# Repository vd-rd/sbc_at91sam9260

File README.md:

## Description
The second installment in the embedded Linux hardware development learning exercise.
The board is an updated version of the previous [AT91RM9200_SBC](https://github.com/vd-rd/sbc_at91rm9200/).
Detailed documentation and resources can be found in the [docs](docs) and [resources](resources) folders.

Note: the CPU comes in two variants, 208 pin PQFP and 217 pin BGA. The PFQP version is pin compatible with AT91SAM9XE. The BGA version is compatible with the improved AT91SAM9G20 and has its own [board](https://github.com/vd-rd/sbc_at91sam9g20).

### Features
 * CPU - AT91SAM9260 processor (ARM926EJ @ 200MHz)
 * RAM - 1Gb SDRAM max ( 3V3 and 1V8 types supported)
 * NVM - AT45DB dataflash for U-boot
 * microSD card slot
 * microUSB client interface
 * USB host breakout
 * RMII interface for Ethernet
 * standard Apollo.IoT expansion header

### Resources
You can find all necesary information to build or evaluate the module here:
   - [View layout and schematic](https://cadlab.io/project/1695) 
   - [View 3D board render](https://a360.co/2PfLcwq)
   - [Fabrication files](https://github.com/vd-rd/sbc_at91sam9260/releases)

### Current status and changelog
  - v1.1.0 assembled and tested using SAM-BA, AT91Bootstrap, U-Boot and Linux Kernel ported from AT91SAM9260EK and running ok
  - v1.1.0 sent to factory, expected to be ready for assembly and testing in mid June.
  - 17feb2021 - v1.1.0 assembled. Debug via UART and USB functional.
  - 19feb2021 - sam-ba is able to load applets. AT91Bootstrap configured and flashed starting from at91sam9260ekdf_uboot_defconfig
  - 21feb2021 - Preliminary uBoot configured and flashed starting from at91sam9260ek_defconfig

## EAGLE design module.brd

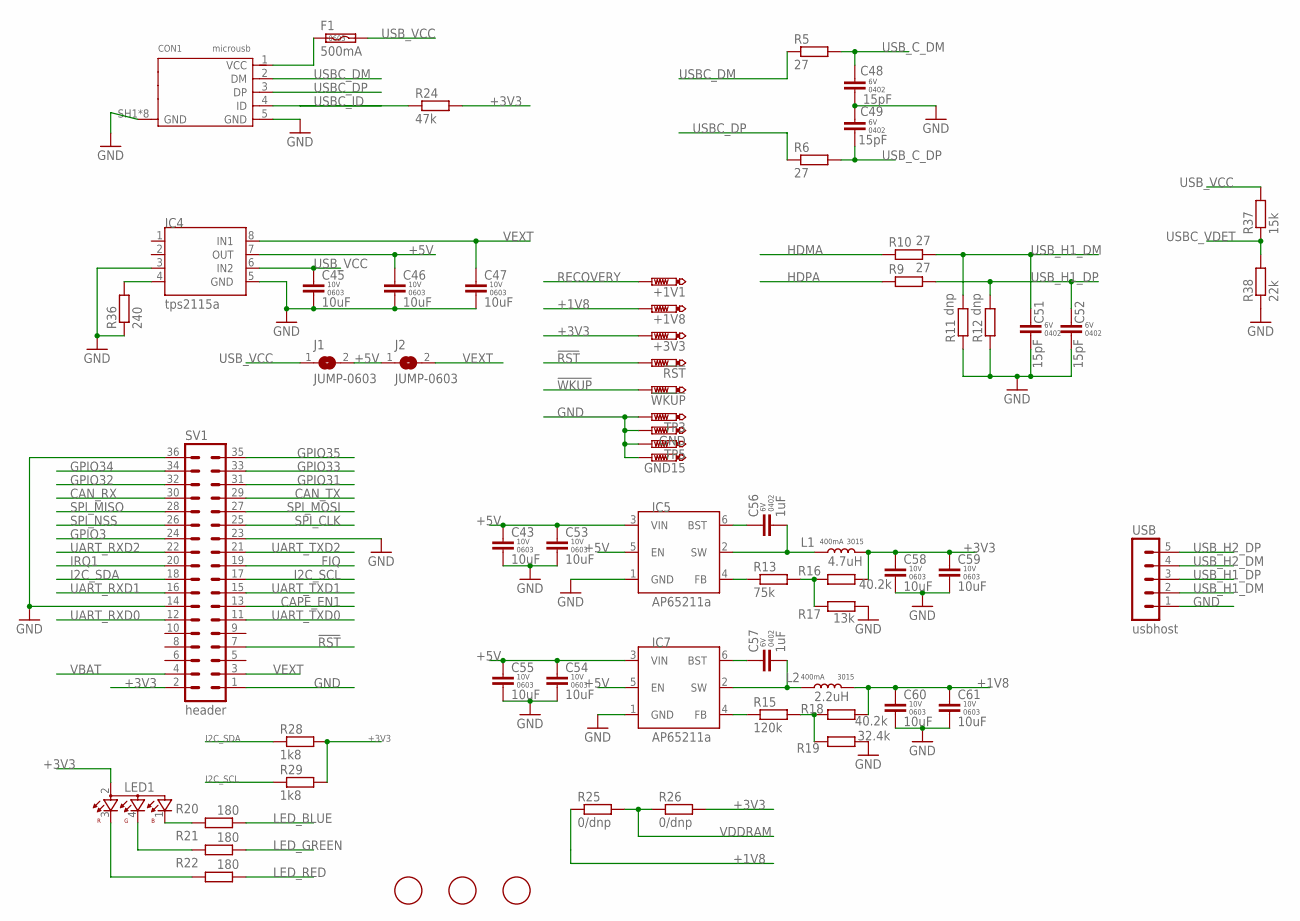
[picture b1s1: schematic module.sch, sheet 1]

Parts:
!RST: PTR1B1,27; B1,27
!WKUP: PTR1B1,27; B1,27
+1V1, +1V8, +3V3: PTR1B1,27; B1,27
C43, C45, C46, C47, C53, C54, C55, C58, C59, C60, C61: 10uF; C0603
C48, C49, C51, C52: 15pF; C0402K
C56, C57: 1uF; C0402K
CON1: microusb; 10118194
F1: 500mA; F0603
GND, GND15: PTR1B1,27; B1,27
IC4: tps2115a; TSSOP8
IC5, IC7: AP65211; SOT95P280X110-6
J1, J2: JUMP-0603; C0603
L1: 4.7uH; L3230M
L2: 2.2uH; L3230M
LED1: OSTB1204C1E; 321015RGB
R5, R6, R9, R10: 27; R0402
R11, R12: dnp; R0402
R13: 75k; R0402
R15: 120k; R0402
R16, R18: 40.2k; R0402
R17: 13k; R0402
R19: 32.4k; R0402
R20, R21, R22: 180; R0402
R24: 47k; R0402
R25, R26: 0/dnp; R0603
R28, R29: 1k8; R0402
R36: 240; R0402
R37: 15k; R0402
R38: 22k; R0402
SV1: header; MA18-2
TP3, TP5: PTR1B1,27; B1,27
U$1, U$2, U$3: FIDUCIAL; FIDUCIAL_1MM
USB: usbhost; MA05-1

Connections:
!RST: !RST.TP, SV1.7; also elsewhere on the board
!WKUP: !WKUP.TP; also elsewhere on the board
+1V8: +1V8.TP, C60.1, C61.1, L2.2, R18.2, R25.1; also elsewhere on the board
+3V3: +3V3.TP, C58.1, C59.1, L1.2, LED1.2, R16.2, R24.2, R26.2, R28.2, R29.2, SV1.2; also elsewhere on the board
+5V: C43.1, C46.1, C53.1, C54.1, C55.1, IC4.7 (OUT), IC5.3 (VIN), IC5.5 (EN), IC7.3 (VIN), IC7.5 (EN), J1.2, J2.1
CAN_RX: SV1.30
CAN_TX: SV1.29
CAPE_EN1: SV1.13; also elsewhere on the board
FIQ: SV1.19; also elsewhere on the board
GND: C43.2, C45.2, C46.2, C47.2, C48.2, C49.2, C51.2, C52.2, C53.2, C54.2, C55.2, C58.2, C59.2, C60.2, C61.2, CON1.5 (GND), CON1.SH1 (GND), CON1.SH2 (GND), CON1.SH3 (GND), CON1.SH4 (GND), CON1.SH5 (GND), CON1.SH6 (GND), CON1.SH7 (GND), CON1.SH8 (GND), GND.TP, GND15.TP, IC4.3, IC4.5 (GND), IC5.1 (GND), IC7.1 (GND), R11.1, R12.1, R17.2, R19.2, R36.1, R38.1, SV1.1, SV1.14, SV1.23, SV1.36, TP3.TP, TP5.TP, USB.1; also elsewhere on the board
GPIO3: SV1.24; also elsewhere on the board
GPIO31: SV1.31; also elsewhere on the board
GPIO32: SV1.32; also elsewhere on the board
GPIO33: SV1.33; also elsewhere on the board
GPIO34: SV1.34; also elsewhere on the board
GPIO35: SV1.35; also elsewhere on the board
HDMA: R10.1; also elsewhere on the board
HDPA: R9.1; also elsewhere on the board
I2C_SCL: R29.1, SV1.17; also elsewhere on the board
I2C_SDA: R28.1, SV1.18; also elsewhere on the board
IRQ1: SV1.20; also elsewhere on the board
LED_BLUE: R20.1; also elsewhere on the board
LED_GREEN: R21.1; also elsewhere on the board
LED_RED: R22.1; also elsewhere on the board
unnamed: C56.2, IC5.2 (SW), L1.1
unnamed: CON1.1 (VCC), F1.1
unnamed: IC4.4, R36.2
unnamed: C57.2, IC7.2 (SW), L2.1
unnamed: LED1.1, R20.2
unnamed: C56.1, IC5.6 (BST)
unnamed: C57.1, IC7.6 (BST)
unnamed: LED1.4, R21.2
unnamed: IC7.4 (FB), R15.1
unnamed: IC5.4 (FB), R13.1
unnamed: R15.2, R18.1, R19.1
unnamed: R13.2, R16.1, R17.1
unnamed: LED1.3, R22.2
RECOVERY: +1V1.TP; also elsewhere on the board
SPI_CLK: SV1.25; also elsewhere on the board
SPI_MISO: SV1.28; also elsewhere on the board
SPI_MOSI: SV1.27; also elsewhere on the board
SPI_NSS: SV1.26; also elsewhere on the board
UART_RXD0: SV1.12; also elsewhere on the board
UART_RXD1: SV1.16; also elsewhere on the board
UART_RXD2: SV1.22; also elsewhere on the board
UART_TXD0: SV1.11; also elsewhere on the board
UART_TXD1: SV1.15; also elsewhere on the board
UART_TXD2: SV1.21; also elsewhere on the board
USBC_DM: CON1.2 (DM), R5.1
USBC_DP: CON1.3 (DP), R6.1
USBC_ID: CON1.4 (ID), R24.1; also elsewhere on the board
USBC_VDET: R37.1, R38.2; also elsewhere on the board
USB_C_DM: C48.1, R5.2; also elsewhere on the board
USB_C_DP: C49.1, R6.2; also elsewhere on the board
USB_H1_DM: C51.1, R10.2, R11.2, USB.2
USB_H1_DP: C52.1, R9.2, R12.2, USB.3
USB_H2_DM: USB.4
USB_H2_DP: USB.5
USB_VCC: C45.1, F1.2, IC4.6 (IN2), J1.1, R37.2
VBAT: SV1.4
VDDRAM: R25.2, R26.1; also elsewhere on the board
VEXT: C47.1, IC4.8 (IN1), J2.2, SV1.3

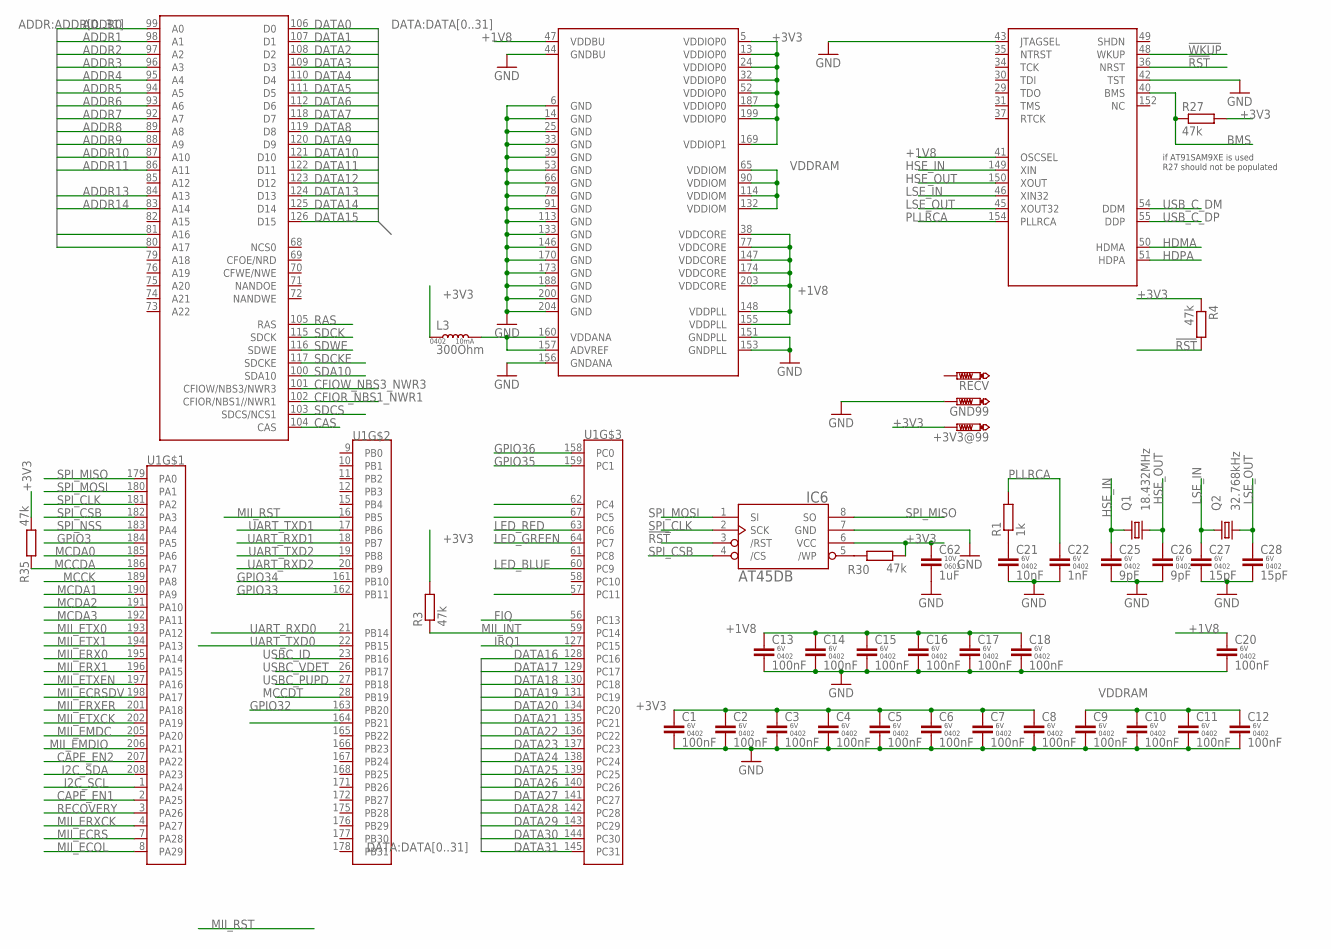
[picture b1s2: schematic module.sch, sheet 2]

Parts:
+3V3@99: PTR1B1,27; B1,27
C1, C2, C3, C4, C5, C6, C7, C8, C9, C10, C11, C12, C13, C14, C15, C16, C17, C18, C20: 100nF; C0402K
C21: 10nF; C0402K
C22: 1nF; C0402K
C25, C26: 9pF; C0402K
C27, C28: 15pF; C0402K
C62: 1uF; C0603
GND99: PTR1B1,27; B1,27
IC6: AT45DB-S; SO08-208
L3: 300Ohm; L0402
Q1: 18.432MHz; 3215
Q2: 32.768kHz; 3215
R1: 1k; R0402
R3, R4, R27, R30, R35: 47k; R0402
RECV: PTR1B1,27; B1,27
U1: AT91SAM9260-; QFP50P3120X3120X410-208N

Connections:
!RST: IC6.3 (/RST), R4.2, U1.36 (NRST); also elsewhere on the board
!WKUP: U1.48 (WKUP); also elsewhere on the board
+1V8: C13.1, C14.1, C15.1, C16.1, C17.1, C18.1, C20.1, U1.38 (VDDCORE), U1.41 (OSCSEL), U1.47 (VDDBU), U1.77 (VDDCORE), U1.147 (VDDCORE), U1.148 (VDDPLL), U1.155 (VDDPLL), U1.174 (VDDCORE), U1.203 (VDDCORE); also elsewhere on the board
+3V3: +3V3@99.TP, C1.1, C2.1, C3.1, C4.1, C5.1, C6.1, C7.1, C8.1, C62.1, IC6.6 (VCC), L3.1, R3.2, R4.1, R27.2, R30.2, R35.2, U1.5 (VDDIOP0), U1.13 (VDDIOP0), U1.24 (VDDIOP0), U1.32 (VDDIOP0), U1.52 (VDDIOP0), U1.169 (VDDIOP1), U1.187 (VDDIOP0), U1.199 (VDDIOP0); also elsewhere on the board
ADDR0: U1.99 (A0); also elsewhere on the board
ADDR1: U1.98 (A1); also elsewhere on the board
ADDR2: U1.97 (A2); also elsewhere on the board
ADDR3: U1.96 (A3); also elsewhere on the board
ADDR4: U1.95 (A4); also elsewhere on the board
ADDR5: U1.94 (A5); also elsewhere on the board
ADDR6: U1.93 (A6); also elsewhere on the board
ADDR7: U1.92 (A7); also elsewhere on the board
ADDR8: U1.89 (A8); also elsewhere on the board
ADDR9: U1.88 (A9); also elsewhere on the board
ADDR10: U1.87 (A10); also elsewhere on the board
ADDR11: U1.86 (A11); also elsewhere on the board
ADDR13: U1.84 (A13); also elsewhere on the board
ADDR14: U1.83 (A14); also elsewhere on the board
ADDR16: U1.81 (A16); also elsewhere on the board
ADDR17: U1.80 (A17); also elsewhere on the board
BMS: R27.1, U1.40 (BMS)
CAPE_EN1: U1.2 (PA25); also elsewhere on the board
CAPE_EN2: U1.207 (PA22)
CAS: U1.104 (CAS); also elsewhere on the board
CFIOR_NBS1_NWR1: U1.102 (CFIOR/NBS1//NWR1); also elsewhere on the board
CFIOW_NBS3_NWR3: U1.101 (CFIOW/NBS3/NWR3); also elsewhere on the board
DATA0: U1.106 (D0); also elsewhere on the board
DATA1: U1.107 (D1); also elsewhere on the board
DATA2: U1.108 (D2); also elsewhere on the board
DATA3: U1.109 (D3); also elsewhere on the board
DATA4: U1.110 (D4); also elsewhere on the board
DATA5: U1.111 (D5); also elsewhere on the board
DATA6: U1.112 (D6); also elsewhere on the board
DATA7: U1.118 (D7); also elsewhere on the board
DATA8: U1.119 (D8); also elsewhere on the board
DATA9: U1.120 (D9); also elsewhere on the board
DATA10: U1.121 (D10); also elsewhere on the board
DATA11: U1.122 (D11); also elsewhere on the board
DATA12: U1.123 (D12); also elsewhere on the board
DATA13: U1.124 (D13); also elsewhere on the board
DATA14: U1.125 (D14); also elsewhere on the board
DATA15: U1.126 (D15); also elsewhere on the board
DATA16: U1.128 (PC16); also elsewhere on the board
DATA17: U1.129 (PC17); also elsewhere on the board
DATA18: U1.130 (PC18); also elsewhere on the board
DATA19: U1.131 (PC19); also elsewhere on the board
DATA20: U1.134 (PC20); also elsewhere on the board
DATA21: U1.135 (PC21); also elsewhere on the board
DATA22: U1.136 (PC22); also elsewhere on the board
DATA23: U1.137 (PC23); also elsewhere on the board
DATA24: U1.138 (PC24); also elsewhere on the board
DATA25: U1.139 (PC25); also elsewhere on the board
DATA26: U1.140 (PC26); also elsewhere on the board
DATA27: U1.141 (PC27); also elsewhere on the board
DATA28: U1.142 (PC28); also elsewhere on the board
DATA29: U1.143 (PC29); also elsewhere on the board
DATA30: U1.144 (PC30); also elsewhere on the board
DATA31: U1.145 (PC31); also elsewhere on the board
FIQ: U1.56 (PC13); also elsewhere on the board
GND: C1.2, C2.2, C3.2, C4.2, C5.2, C6.2, C7.2, C8.2, C9.2, C10.2, C11.2, C12.2, C13.2, C14.2, C15.2, C16.2, C17.2, C18.2, C20.2, C21.2, C22.2, C25.2, C26.2, C27.2, C28.2, C62.2, GND99.TP, IC6.7 (GND), U1.6 (GND), U1.14 (GND), U1.25 (GND), U1.33 (GND), U1.39 (GND), U1.42 (TST), U1.43 (JTAGSEL), U1.44 (GNDBU), U1.53 (GND), U1.66 (GND), U1.78 (GND), U1.91 (GND), U1.113 (GND), U1.133 (GND), U1.146 (GND), U1.151 (GNDPLL), U1.153 (GNDPLL), U1.156 (GNDANA), U1.170 (GND), U1.173 (GND), U1.188 (GND), U1.200 (GND), U1.204 (GND); also elsewhere on the board
GPIO3: U1.184 (PA5); also elsewhere on the board
GPIO31: U1.164 (PB21); also elsewhere on the board
GPIO32: U1.163 (PB20); also elsewhere on the board
GPIO33: U1.162 (PB11); also elsewhere on the board
GPIO34: U1.161 (PB10); also elsewhere on the board
GPIO35: U1.159 (PC1); also elsewhere on the board
GPIO36: U1.158 (PC0)
HDMA: U1.50 (HDMA); also elsewhere on the board
HDPA: U1.51 (HDPA); also elsewhere on the board
HSE_IN: C25.1, Q1.1, U1.149 (XIN)
HSE_OUT: C26.1, Q1.3 (2), U1.150 (XOUT)
I2C_SCL: U1.1 (PA24); also elsewhere on the board
I2C_SDA: U1.208 (PA23); also elsewhere on the board
IRQ1: U1.127 (PC15); also elsewhere on the board
LED_BLUE: U1.60 (PC9); also elsewhere on the board
LED_GREEN: U1.64 (PC7); also elsewhere on the board
LED_RED: U1.63 (PC6); also elsewhere on the board
LSE_IN: C27.1, Q2.1, U1.46 (XIN32)
LSE_OUT: C28.1, Q2.2, U1.45 (XOUT32)
MCCDA: R35.1, U1.186 (PA7); also elsewhere on the board
MCCDT: U1.28 (PB19); also elsewhere on the board
MCCK: U1.189 (PA8); also elsewhere on the board
MCDA0: U1.185 (PA6); also elsewhere on the board
MCDA1: U1.190 (PA9); also elsewhere on the board
MCDA2: U1.191 (PA10); also elsewhere on the board
MCDA3: U1.192 (PA11); also elsewhere on the board
MII_ECOL: U1.8 (PA29)
MII_ECRS: U1.7 (PA28)
MII_ECRSDV: U1.198 (PA17); also elsewhere on the board
MII_EMDC: U1.205 (PA20); also elsewhere on the board
MII_EMDIO: U1.206 (PA21); also elsewhere on the board
MII_ERX0: U1.195 (PA14); also elsewhere on the board
MII_ERX1: U1.196 (PA15); also elsewhere on the board
MII_ERXCK: U1.4 (PA27)
MII_ERXER: U1.201 (PA18); also elsewhere on the board
MII_ETX0: U1.193 (PA12); also elsewhere on the board
MII_ETX1: U1.194 (PA13); also elsewhere on the board
MII_ETXCK: U1.202 (PA19); also elsewhere on the board
MII_ETXEN: U1.197 (PA16); also elsewhere on the board
MII_INT: R3.1, U1.59 (PC14); also elsewhere on the board
MII_RST: U1.16 (PB5); also elsewhere on the board
unnamed: C21.1, R1.1
unnamed: IC6.5 (/WP), R30.1
unnamed: L3.2, U1.157 (ADVREF), U1.160 (VDDANA)
PLLRCA: C22.1, R1.2, U1.154 (PLLRCA)
RAS: U1.105 (RAS); also elsewhere on the board
RECOVERY: U1.3 (PA26); also elsewhere on the board
SDA10: U1.100 (SDA10); also elsewhere on the board
SDCK: U1.115 (SDCK); also elsewhere on the board
SDCKE: U1.117 (SDCKE); also elsewhere on the board
SDCS: U1.103 (SDCS/NCS1); also elsewhere on the board
SDWE: U1.116 (SDWE); also elsewhere on the board
SPI_CLK: IC6.2 (SCK), U1.181 (PA2); also elsewhere on the board
SPI_CSB: IC6.4 (/CS), U1.182 (PA3)
SPI_MISO: IC6.8 (SO), U1.179 (PA0); also elsewhere on the board
SPI_MOSI: IC6.1 (SI), U1.180 (PA1); also elsewhere on the board
SPI_NSS: U1.183 (PA4); also elsewhere on the board
UART_RXD0: U1.21 (PB14); also elsewhere on the board
UART_RXD1: U1.18 (PB7); also elsewhere on the board
UART_RXD2: U1.20 (PB9); also elsewhere on the board
UART_TXD0: U1.22 (PB15); also elsewhere on the board
UART_TXD1: U1.17 (PB6); also elsewhere on the board
UART_TXD2: U1.19 (PB8); also elsewhere on the board
USBC_ID: U1.23 (PB16); also elsewhere on the board
USBC_PUPD: U1.27 (PB18)
USBC_VDET: U1.26 (PB17); also elsewhere on the board
USB_C_DM: U1.54 (DDM); also elsewhere on the board
USB_C_DP: U1.55 (DDP); also elsewhere on the board
VDDRAM: C9.1, C10.1, C11.1, C12.1, U1.65 (VDDIOM), U1.90 (VDDIOM), U1.114 (VDDIOM), U1.132 (VDDIOM); also elsewhere on the board

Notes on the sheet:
if AT91SAM9XE is used R27 should not be populated

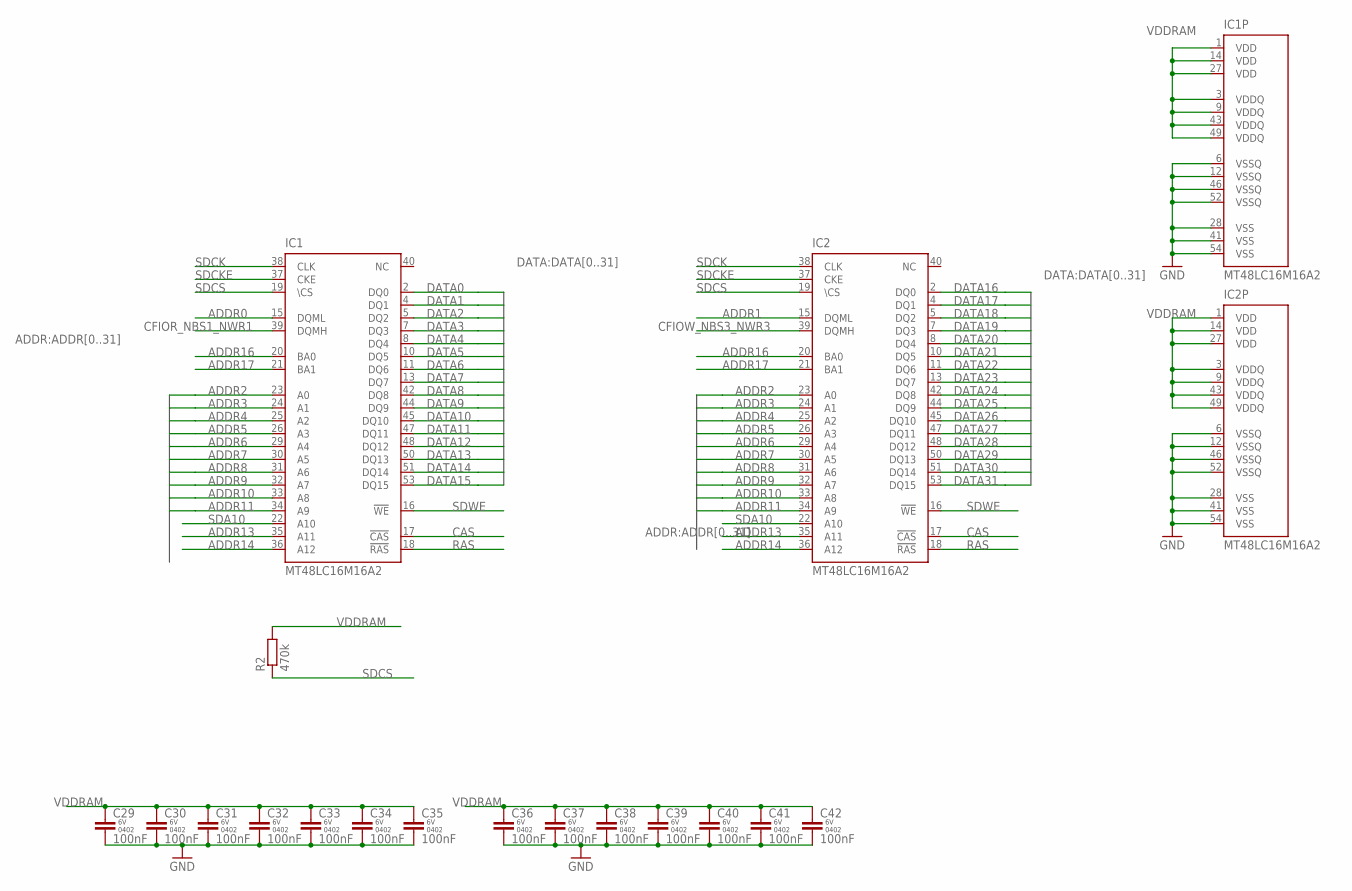
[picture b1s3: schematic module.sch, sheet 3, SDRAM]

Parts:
C29, C30, C31, C32, C33, C34, C35, C36, C37, C38, C39, C40, C41, C42: 100nF; C0402K
IC1, IC2: MT48LC16M16A2; TSOP54-400
R2: 470k; R0402

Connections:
ADDR0: IC1.15 (DQML); also elsewhere on the board
ADDR1: IC2.15 (DQML); also elsewhere on the board
ADDR2: IC1.23 (A0), IC2.23 (A0); also elsewhere on the board
ADDR3: IC1.24 (A1), IC2.24 (A1); also elsewhere on the board
ADDR4: IC1.25 (A2), IC2.25 (A2); also elsewhere on the board
ADDR5: IC1.26 (A3), IC2.26 (A3); also elsewhere on the board
ADDR6: IC1.29 (A4), IC2.29 (A4); also elsewhere on the board
ADDR7: IC1.30 (A5), IC2.30 (A5); also elsewhere on the board
ADDR8: IC1.31 (A6), IC2.31 (A6); also elsewhere on the board
ADDR9: IC1.32 (A7), IC2.32 (A7); also elsewhere on the board
ADDR10: IC1.33 (A8), IC2.33 (A8); also elsewhere on the board
ADDR11: IC1.34 (A9), IC2.34 (A9); also elsewhere on the board
ADDR13: IC1.35 (A11), IC2.35 (A11); also elsewhere on the board
ADDR14: IC1.36 (A12), IC2.36 (A12); also elsewhere on the board
ADDR16: IC1.20 (BA0), IC2.20 (BA0); also elsewhere on the board
ADDR17: IC1.21 (BA1), IC2.21 (BA1); also elsewhere on the board
CAS: IC1.17 (!CAS), IC2.17 (!CAS); also elsewhere on the board
CFIOR_NBS1_NWR1: IC1.39 (DQMH); also elsewhere on the board
CFIOW_NBS3_NWR3: IC2.39 (DQMH); also elsewhere on the board
DATA0: IC1.2 (DQ0); also elsewhere on the board
DATA1: IC1.4 (DQ1); also elsewhere on the board
DATA2: IC1.5 (DQ2); also elsewhere on the board
DATA3: IC1.7 (DQ3); also elsewhere on the board
DATA4: IC1.8 (DQ4); also elsewhere on the board
DATA5: IC1.10 (DQ5); also elsewhere on the board
DATA6: IC1.11 (DQ6); also elsewhere on the board
DATA7: IC1.13 (DQ7); also elsewhere on the board
DATA8: IC1.42 (DQ8); also elsewhere on the board
DATA9: IC1.44 (DQ9); also elsewhere on the board
DATA10: IC1.45 (DQ10); also elsewhere on the board
DATA11: IC1.47 (DQ11); also elsewhere on the board
DATA12: IC1.48 (DQ12); also elsewhere on the board
DATA13: IC1.50 (DQ13); also elsewhere on the board
DATA14: IC1.51 (DQ14); also elsewhere on the board
DATA15: IC1.53 (DQ15); also elsewhere on the board
DATA16: IC2.2 (DQ0); also elsewhere on the board
DATA17: IC2.4 (DQ1); also elsewhere on the board
DATA18: IC2.5 (DQ2); also elsewhere on the board
DATA19: IC2.7 (DQ3); also elsewhere on the board
DATA20: IC2.8 (DQ4); also elsewhere on the board
DATA21: IC2.10 (DQ5); also elsewhere on the board
DATA22: IC2.11 (DQ6); also elsewhere on the board
DATA23: IC2.13 (DQ7); also elsewhere on the board
DATA24: IC2.42 (DQ8); also elsewhere on the board
DATA25: IC2.44 (DQ9); also elsewhere on the board
DATA26: IC2.45 (DQ10); also elsewhere on the board
DATA27: IC2.47 (DQ11); also elsewhere on the board
DATA28: IC2.48 (DQ12); also elsewhere on the board
DATA29: IC2.50 (DQ13); also elsewhere on the board
DATA30: IC2.51 (DQ14); also elsewhere on the board
DATA31: IC2.53 (DQ15); also elsewhere on the board
GND: C29.2, C30.2, C31.2, C32.2, C33.2, C34.2, C35.2, C36.2, C37.2, C38.2, C39.2, C40.2, C41.2, C42.2, IC1.6 (VSSQ), IC1.12 (VSSQ), IC1.28 (VSS), IC1.41 (VSS), IC1.46 (VSSQ), IC1.52 (VSSQ), IC1.54 (VSS), IC2.6 (VSSQ), IC2.12 (VSSQ), IC2.28 (VSS), IC2.41 (VSS), IC2.46 (VSSQ), IC2.52 (VSSQ), IC2.54 (VSS); also elsewhere on the board
RAS: IC1.18 (!RAS), IC2.18 (!RAS); also elsewhere on the board
SDA10: IC1.22 (A10), IC2.22 (A10); also elsewhere on the board
SDCK: IC1.38 (CLK), IC2.38 (CLK); also elsewhere on the board
SDCKE: IC1.37 (CKE), IC2.37 (CKE); also elsewhere on the board
SDCS: IC1.19 (\CS), IC2.19 (\CS), R2.1; also elsewhere on the board
SDWE: IC1.16 (!WE), IC2.16 (!WE); also elsewhere on the board
VDDRAM: C29.1, C30.1, C31.1, C32.1, C33.1, C34.1, C35.1, C36.1, C37.1, C38.1, C39.1, C40.1, C41.1, C42.1, IC1.1 (VDD), IC1.3 (VDDQ), IC1.9 (VDDQ), IC1.14 (VDD), IC1.27 (VDD), IC1.43 (VDDQ), IC1.49 (VDDQ), IC2.1 (VDD), IC2.3 (VDDQ), IC2.9 (VDDQ), IC2.14 (VDD), IC2.27 (VDD), IC2.43 (VDDQ), IC2.49 (VDDQ), R2.2; also elsewhere on the board

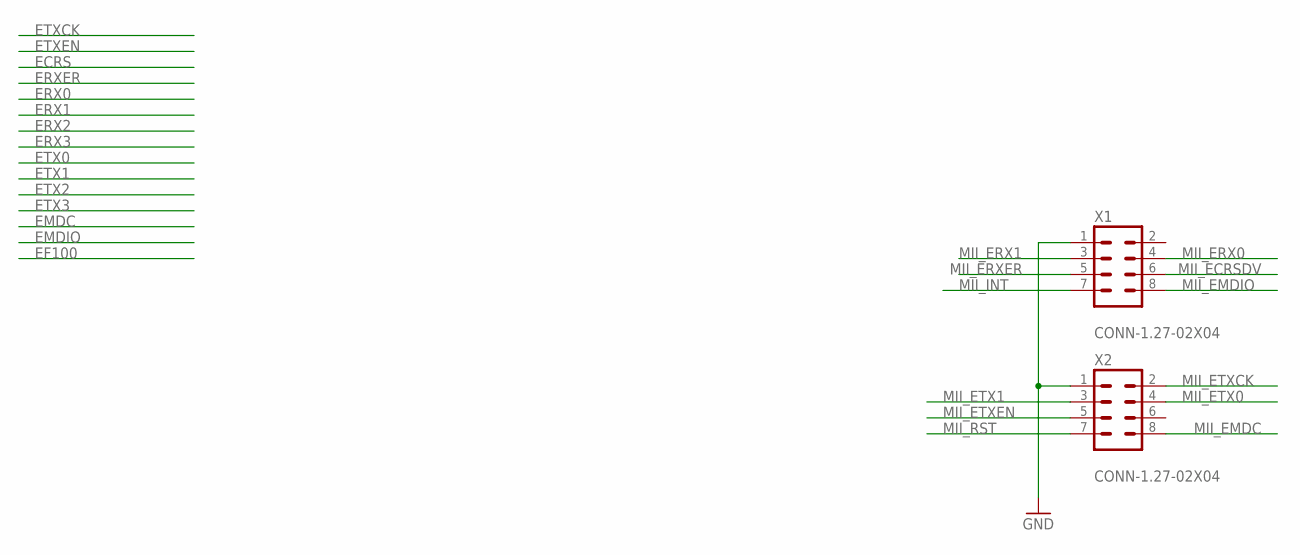
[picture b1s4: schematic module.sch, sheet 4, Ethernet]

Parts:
X1, X2: CONN-1.27-02X04; 050_610_HN-5/10

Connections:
GND: X1.1, X2.1; also elsewhere on the board
MII_ECRSDV: X1.6; also elsewhere on the board
MII_EMDC: X2.8; also elsewhere on the board
MII_EMDIO: X1.8; also elsewhere on the board
MII_ERX0: X1.4; also elsewhere on the board
MII_ERX1: X1.3; also elsewhere on the board
MII_ERXER: X1.5; also elsewhere on the board
MII_ETX0: X2.4; also elsewhere on the board
MII_ETX1: X2.3; also elsewhere on the board
MII_ETXCK: X2.2; also elsewhere on the board
MII_ETXEN: X2.5; also elsewhere on the board
MII_INT: X1.7; also elsewhere on the board
MII_RST: X2.7; also elsewhere on the board

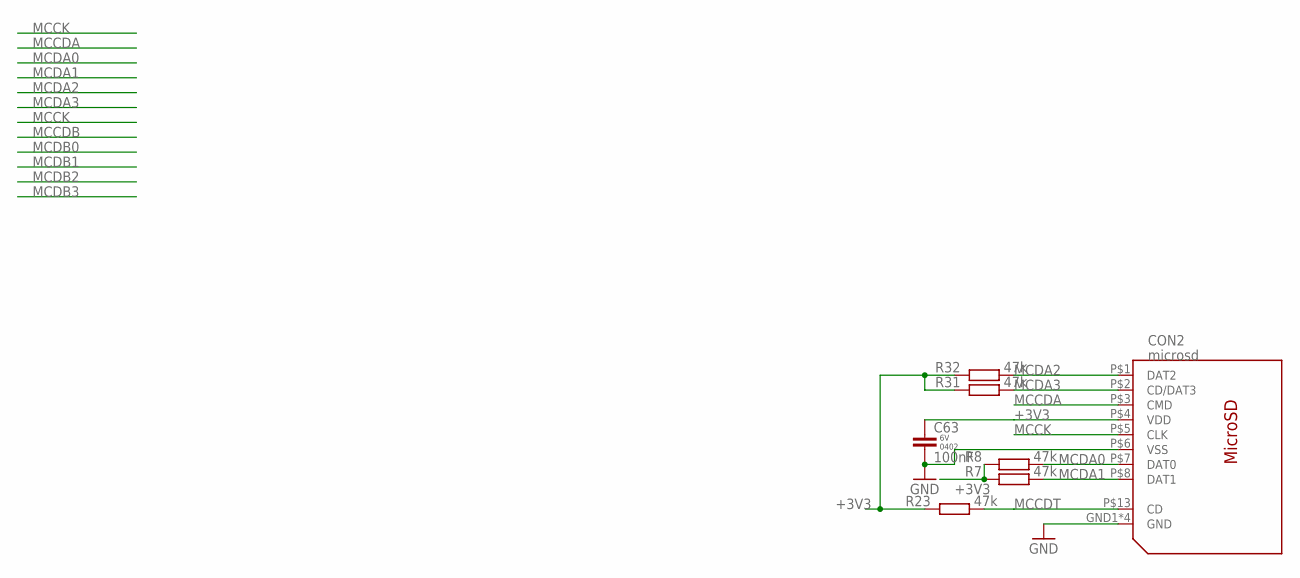
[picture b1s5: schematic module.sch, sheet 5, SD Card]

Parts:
C63: 100nF; C0402K
CON2: microsd; 112J
R7, R8, R23, R31, R32: 47k; R0402

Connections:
+3V3: C63.1, CON2.P$4 (VDD), R7.1, R8.1, R23.1, R31.1, R32.1; also elsewhere on the board
GND: C63.2, CON2.GND1 (GND), CON2.GND2 (GND), CON2.GND3 (GND), CON2.GND4 (GND), CON2.P$6 (VSS); also elsewhere on the board
MCCDA: CON2.P$3 (CMD); also elsewhere on the board
MCCDT: CON2.P$13 (CD), R23.2; also elsewhere on the board
MCCK: CON2.P$5 (CLK); also elsewhere on the board
MCDA0: CON2.P$7 (DAT0), R8.2; also elsewhere on the board
MCDA1: CON2.P$8 (DAT1), R7.2; also elsewhere on the board
MCDA2: CON2.P$1 (DAT2), R32.2; also elsewhere on the board
MCDA3: CON2.P$2 (CD/DAT3), R31.2; also elsewhere on the board

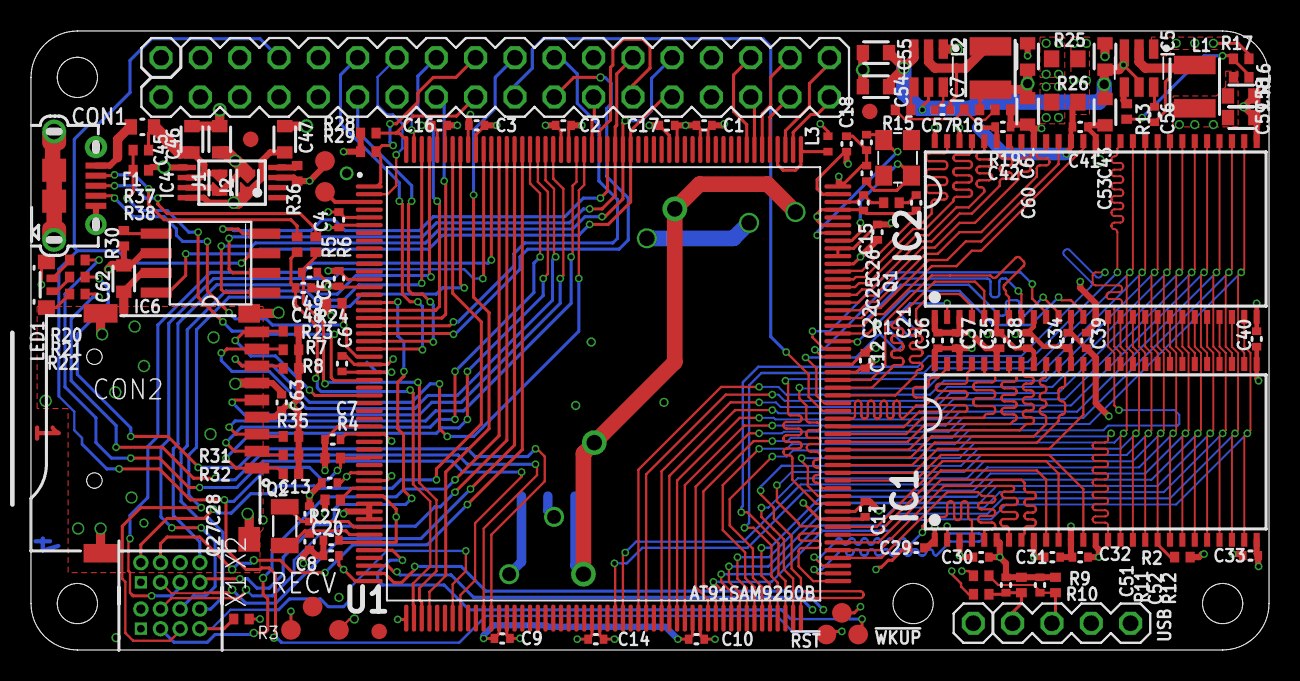
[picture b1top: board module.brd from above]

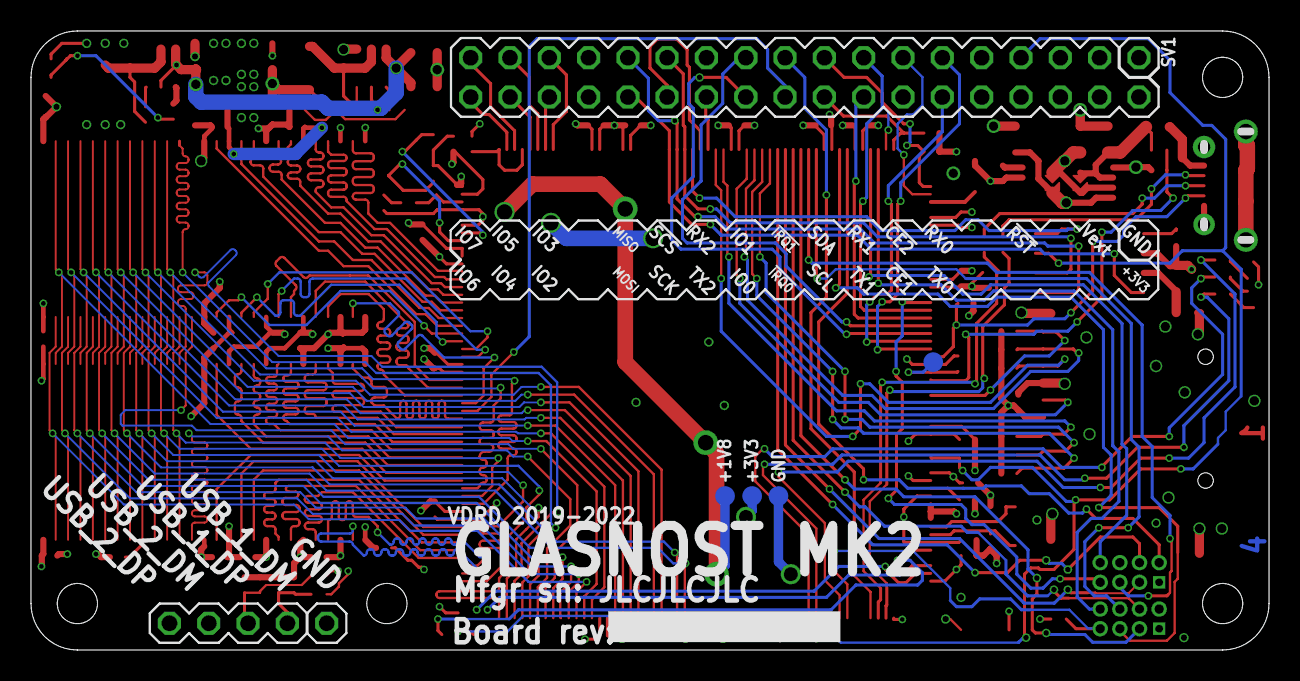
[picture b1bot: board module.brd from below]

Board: 4 copper layers, 80.0 x 40.0 mm, 130 parts (5 on the bottom side), 143 nets.

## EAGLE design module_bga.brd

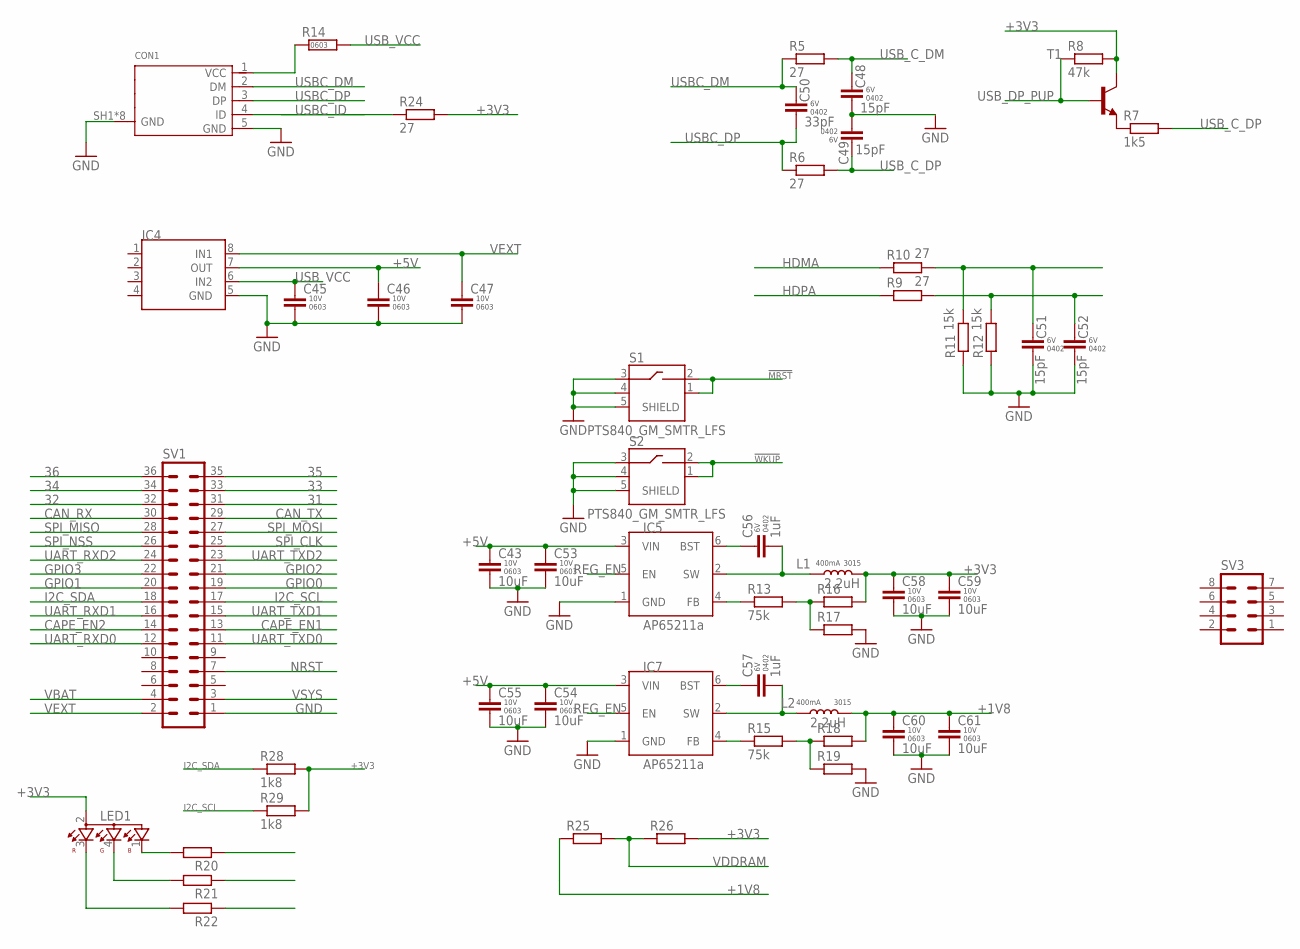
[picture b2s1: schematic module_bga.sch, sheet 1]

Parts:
C43, C53, C54, C55, C58, C59, C60, C61: 10uF; C0603
C45, C46, C47: CAP-0603; C0603
C48, C49, C51, C52: 15pF; C0402K
C50: 33pF; C0402K
C56, C57: 1uF; C0402K
CON1: 10118194-0001LF; 10118194
IC4: TPS2115A; TSSOP8
IC5, IC7: AP65211; SOT95P280X110-6
L1, L2: 2.2uH; L3230M
LED1: OSTB1204C1E; 321015RGB
R5, R6, R9, R10, R24: 27; R0402
R7: 1k5; R0402
R8: 47k; R0402
R11, R12: 15k; R0402
R13, R15: 75k; R0402
R14: RES-0603; R0603
R16, R17, R18, R19, R20, R21, R22: R-EU_R0402; R0402
R25, R26: R-EU_R0603; R0603
R28, R29: 1k8; R0402
S1, S2: PTS840_GM_SMTR_LFS; SW_PTS840GMSMTRLFS
SV1: MA18-2
SV3: MA04-2
T1: MMBT2222ALT1-NPN-SOT23-BEC; SOT23-BEC

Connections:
31: SV1.31
32: SV1.32
33: SV1.33
34: SV1.34
35: SV1.35
36: SV1.36
!MRST: S1.1, S1.2; also elsewhere on the board
!WKUP: S2.1, S2.2; also elsewhere on the board
+1V8: C60.1, C61.1, L2.2, R18.2, R25.1; also elsewhere on the board
+3V3: C58.1, C59.1, L1.2, LED1.2, R8.2, R16.2, R24.2, R26.2, R28.2, R29.2, T1.C; also elsewhere on the board
+5V: C43.1, C46.1, C53.1, C54.1, C55.1, IC4.7 (OUT), IC5.3 (VIN), IC7.3 (VIN)
CAN_RX: SV1.30
CAN_TX: SV1.29
CAPE_EN1: SV1.13
CAPE_EN2: SV1.14
GND: C43.2, C45.2, C46.2, C47.2, C48.2, C49.2, C51.2, C52.2, C53.2, C54.2, C55.2, C58.2, C59.2, C60.2, C61.2, CON1.5 (GND), CON1.SH1 (GND), CON1.SH2 (GND), CON1.SH3 (GND), CON1.SH4 (GND), CON1.SH5 (GND), CON1.SH6 (GND), CON1.SH7 (GND), CON1.SH8 (GND), IC4.5 (GND), IC5.1 (GND), IC7.1 (GND), R11.1, R12.1, R17.2, R19.2, S1.3, S1.4, S1.5 (SHIELD), S2.3, S2.4, S2.5 (SHIELD), SV1.1; also elsewhere on the board
GPIO0: SV1.19
GPIO1: SV1.20
GPIO2: SV1.21
GPIO3: SV1.22
HDMA: R10.1; also elsewhere on the board
HDPA: R9.1; also elsewhere on the board
I2C_SCL: R29.1, SV1.17; also elsewhere on the board
I2C_SDA: R28.1, SV1.18; also elsewhere on the board
unnamed: C56.2, IC5.2 (SW), L1.1
unnamed: CON1.1 (VCC), R14.1
unnamed: C57.2, IC7.2 (SW), L2.1
unnamed: LED1.1, R20.2
unnamed: C56.1, IC5.6 (BST)
unnamed: C57.1, IC7.6 (BST)
unnamed: C52.1, R9.2, R12.2
unnamed: LED1.4, R21.2
unnamed: IC7.4 (FB), R15.1
unnamed: R7.1, T1.E
unnamed: C51.1, R10.2, R11.2
unnamed: IC5.4 (FB), R13.1
unnamed: R15.2, R18.1, R19.1
unnamed: R13.2, R16.1, R17.1
unnamed: LED1.3, R22.2
NRST: SV1.7; also elsewhere on the board
REG_EN: IC5.5 (EN), IC7.5 (EN)
SPI_CLK: SV1.25; also elsewhere on the board
SPI_MISO: SV1.28; also elsewhere on the board
SPI_MOSI: SV1.27; also elsewhere on the board
SPI_NSS: SV1.26
UART_RXD0: SV1.12; also elsewhere on the board
UART_RXD1: SV1.16; also elsewhere on the board
UART_RXD2: SV1.24; also elsewhere on the board
UART_TXD0: SV1.11; also elsewhere on the board
UART_TXD1: SV1.15; also elsewhere on the board
UART_TXD2: SV1.23; also elsewhere on the board
USBC_DM: C50.1, CON1.2 (DM), R5.1
USBC_DP: C50.2, CON1.3 (DP), R6.1
USBC_ID: CON1.4 (ID), R24.1
USB_C_DM: C48.1, R5.2; also elsewhere on the board
USB_C_DP: C49.1, R6.2, R7.2; also elsewhere on the board
USB_DP_PUP: R8.1, T1.B
USB_VCC: C45.1, IC4.6 (IN2), R14.2
VBAT: SV1.4
VDDRAM: R25.2, R26.1; also elsewhere on the board
VEXT: C47.1, IC4.8 (IN1), SV1.2
VSYS: SV1.3
